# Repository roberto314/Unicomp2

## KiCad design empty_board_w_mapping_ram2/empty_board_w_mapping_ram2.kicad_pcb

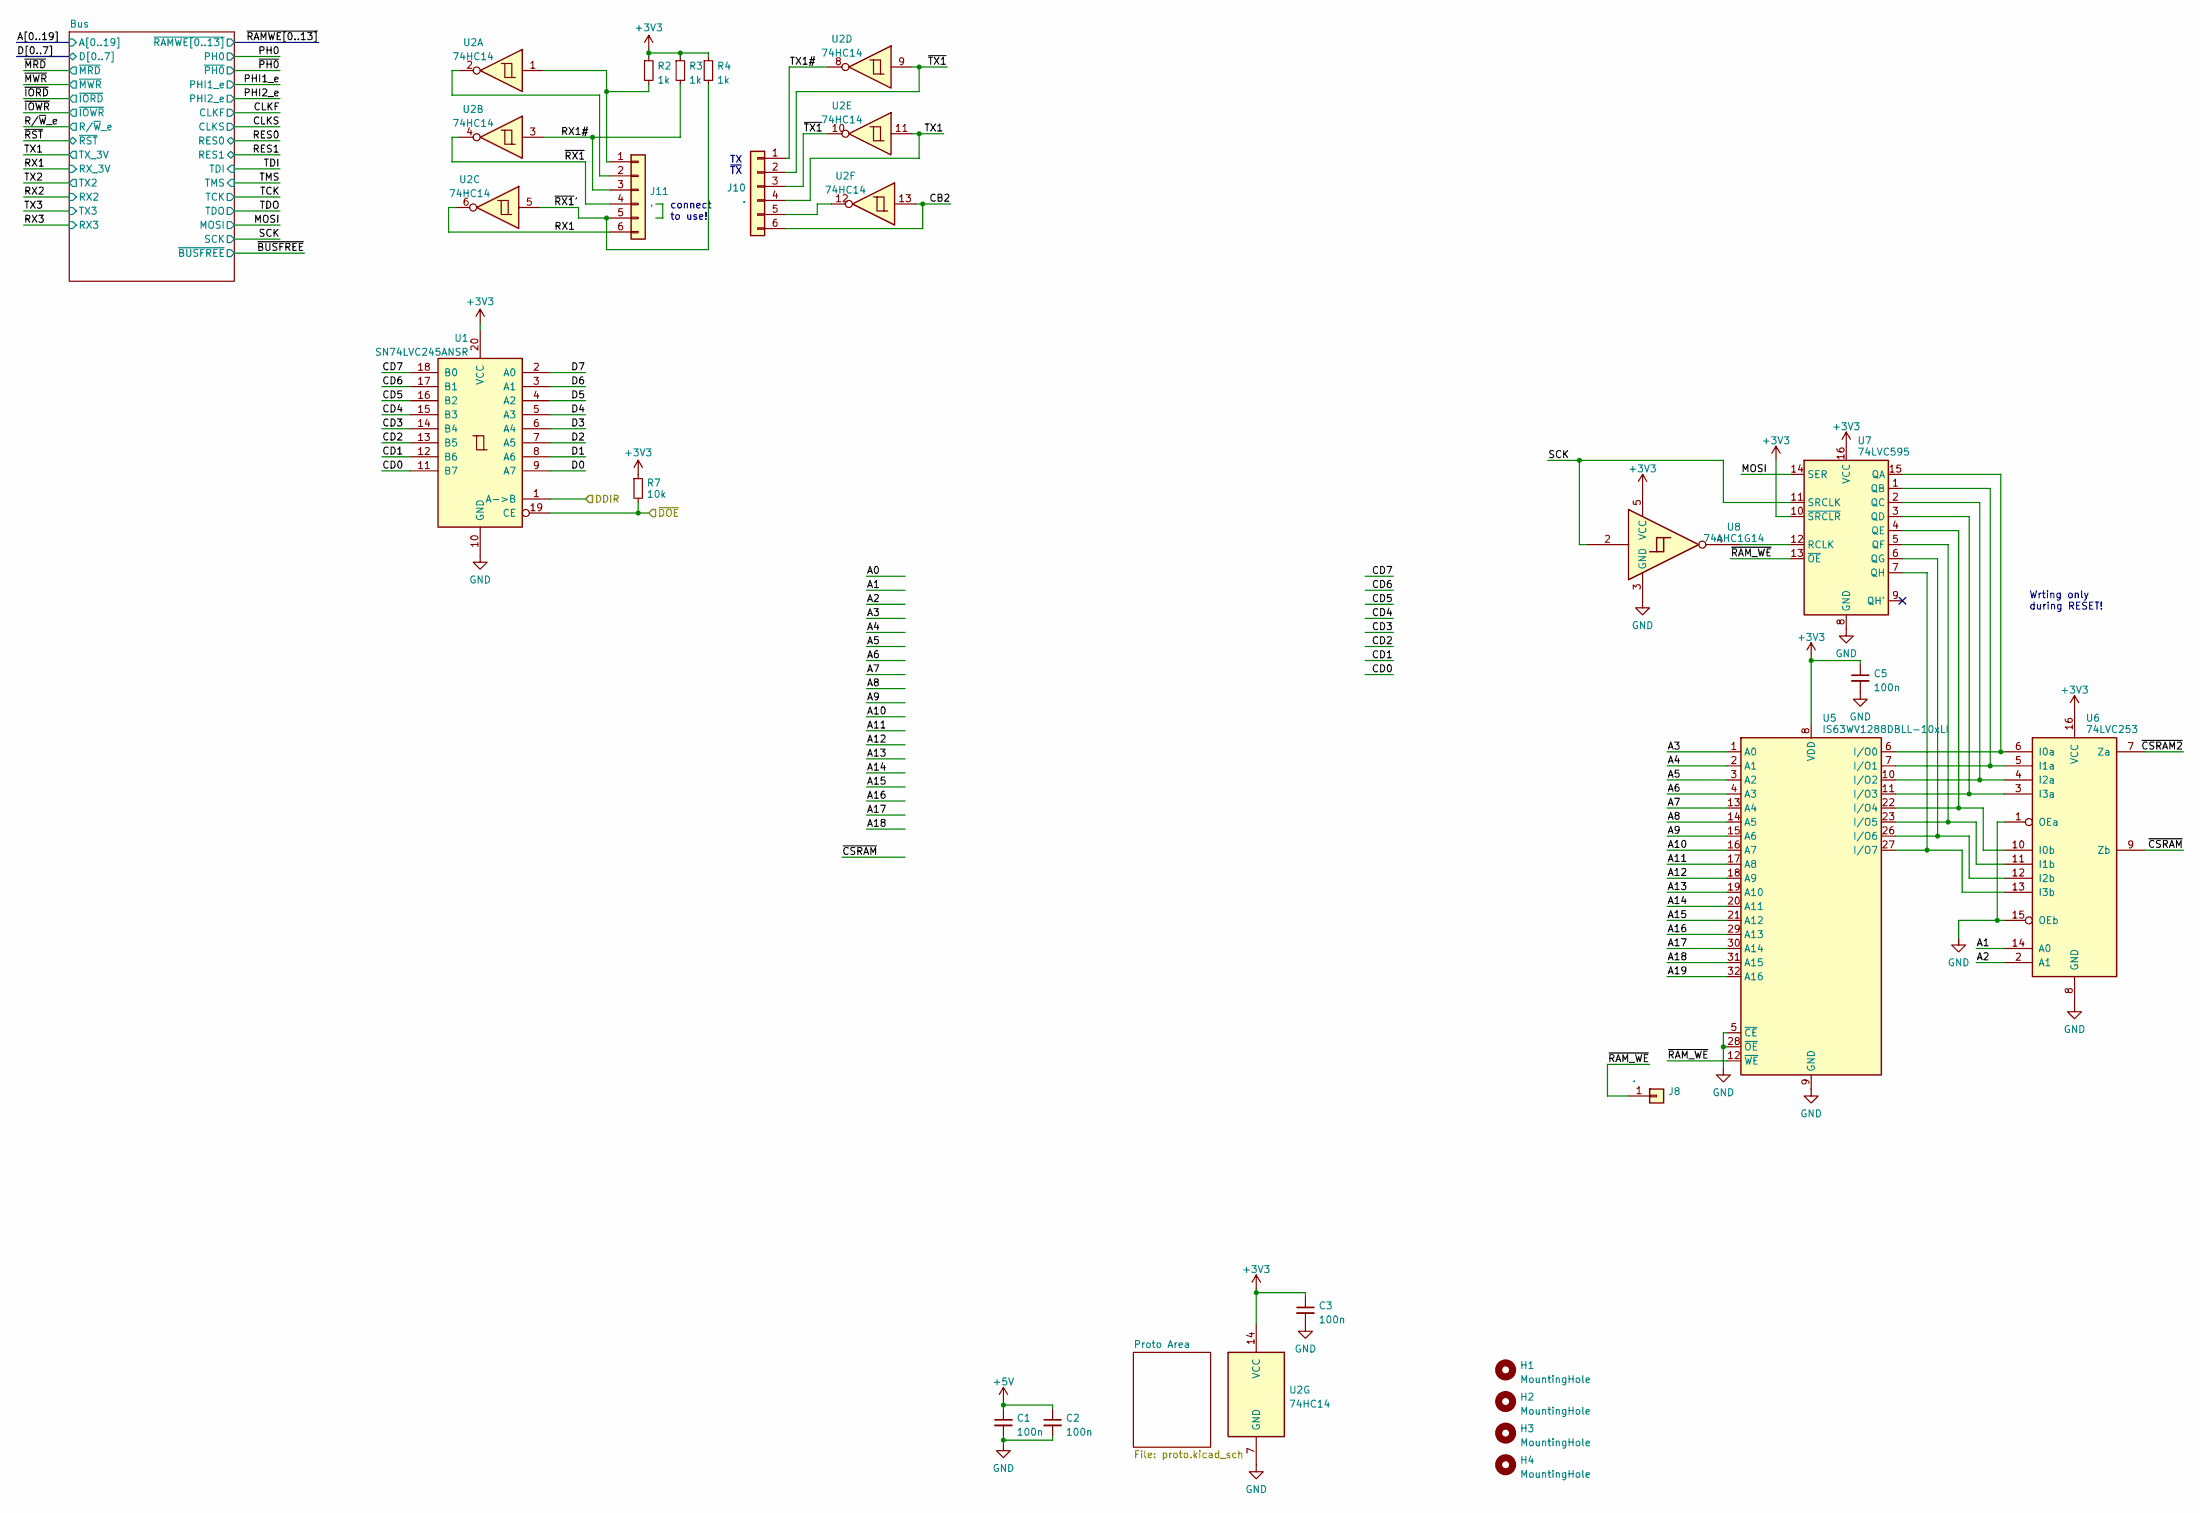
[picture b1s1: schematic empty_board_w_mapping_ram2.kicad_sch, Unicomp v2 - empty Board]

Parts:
C1, C2, C3, C5: 100n; C_1206_3216Metric
H1, H2, H3, H4: MountingHole; MountingHole_3.2mm_M3
J8: .; PinHeader_1x01_P2.00mm_Vertical
J10, J11: .; PinHeader_1x06_P2.54mm_Vertical
R2, R3, R4: 1k; R_1206_3216Metric_Pad1.30x1.75mm_HandSolder
R7: 10k; R_1206_3216Metric_Pad1.30x1.75mm_HandSolder
U1: SN74LVC245ANSR; SO-20_5.3x12.6mm_P1.27mm
U2: 74HC14; DIP-14_W7.62mm_Socket
U5: IS63WV1288DBLL-10xLI; TSOP-II-32_21.0x10.2mm_P1.27mm
U6: 74LVC253; SO-16_3.9x9.9mm_P1.27mm
U7: 74LVC595; SO-16_3.9x9.9mm_P1.27mm
U8: 74AHC1G14; SOT-23-5

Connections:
+3V3: C3.1, C5.1, R2.1, R3.1, R4.1, R7.1, U1.20 (VCC), U2.14 (VCC), U5.8 (VDD), U5.24 (VDD), U6.16 (VCC), U7.10 (~SRCLR), U7.16 (VCC), U8.5 (VCC); also elsewhere on the board
+5V: C1.1, C2.1; also elsewhere on the board
/A1: U6.14 (A0); also elsewhere on the board
/A2: U6.2 (A1); also elsewhere on the board
/A3: U5.1 (A0); also elsewhere on the board
/A4: U5.2 (A1); also elsewhere on the board
/A5: U5.3 (A2); also elsewhere on the board
/A6: U5.4 (A3); also elsewhere on the board
/A7: U5.13 (A4); also elsewhere on the board
/A8: U5.14 (A5); also elsewhere on the board
/A9: U5.15 (A6); also elsewhere on the board
/A10: U5.16 (A7); also elsewhere on the board
/A11: U5.17 (A8); also elsewhere on the board
/A12: U5.18 (A9); also elsewhere on the board
/A13: U5.19 (A10); also elsewhere on the board
/A14: U5.20 (A11); also elsewhere on the board
/A15: U5.21 (A12); also elsewhere on the board
/A16: U5.29 (A13); also elsewhere on the board
/A17: U5.30 (A14); also elsewhere on the board
/A18: U5.31 (A15); also elsewhere on the board
/A19: U5.32 (A16); also elsewhere on the board
/CB2: J10.6, U2.13
/CD0: U1.11 (B7)
/CD1: U1.12 (B6)
/CD2: U1.13 (B5)
/CD3: U1.14 (B4)
/CD4: U1.15 (B3)
/CD5: U1.16 (B2)
/CD6: U1.17 (B1)
/CD7: U1.18 (B0)
/D0: U1.9 (A7); also elsewhere on the board
/D1: U1.8 (A6); also elsewhere on the board
/D2: U1.7 (A5); also elsewhere on the board
/D3: U1.6 (A4); also elsewhere on the board
/D4: U1.5 (A3); also elsewhere on the board
/D5: U1.4 (A2); also elsewhere on the board
/D6: U1.3 (A1); also elsewhere on the board
/D7: U1.2 (A0); also elsewhere on the board
/DDIR: U1.1 (A->B)
/MOSI: U7.14 (SER); also elsewhere on the board
/RX1: J11.6, U2.6; also elsewhere on the board
/RX1#: J11.3, R3.2, U2.3
/SCK: U7.11 (SRCLK), U8.2; also elsewhere on the board
/TX1: J10.4, U2.11; also elsewhere on the board
/TX1#: J10.1, U2.8
/~CSRAM2: U6.7 (Za)
/~CSRAM: U6.9 (Zb)
/~DOE: R7.2, U1.19 (CE)
/~RAM_WE: J8.1, U5.12 (~WE), U7.13 (~OE)
/~RX1: J11.4, U2.4
/~RX1': J11.5, R4.2, U2.5
/~TX1: J10.2, J10.3, U2.9, U2.10
GND: C1.2, C2.2, C3.2, C5.2, U1.10 (GND), U2.7 (GND), U5.5 (~CE), U5.9 (GND), U5.25 (GND), U5.28 (~OE), U6.1 (OEa), U6.8 (GND), U6.15 (OEb), U7.8 (GND), U8.3 (GND); also elsewhere on the board
unnamed: J10.5, U2.12
unnamed: J11.1, R2.2, U2.1
unnamed: J11.2, U2.2
unnamed: U5.6 (I/O0), U6.6 (I0a), U7.15 (QA)
unnamed: U5.7 (I/O1), U6.5 (I1a), U7.1 (QB)
unnamed: U5.10 (I/O2), U6.4 (I2a), U7.2 (QC)
unnamed: U5.11 (I/O3), U6.3 (I3a), U7.3 (QD)
unnamed: U5.22 (I/O4), U6.10 (I0b), U7.4 (QE)
unnamed: U5.23 (I/O5), U6.11 (I1b), U7.5 (QF)
unnamed: U5.26 (I/O6), U6.12 (I2b), U7.6 (QG)
unnamed: U5.27 (I/O7), U6.13 (I3b), U7.7 (QH)
unnamed: U7.12 (RCLK), U8.4

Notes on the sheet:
Wrting only during RESET!
connect to use!
TX ~{TX}

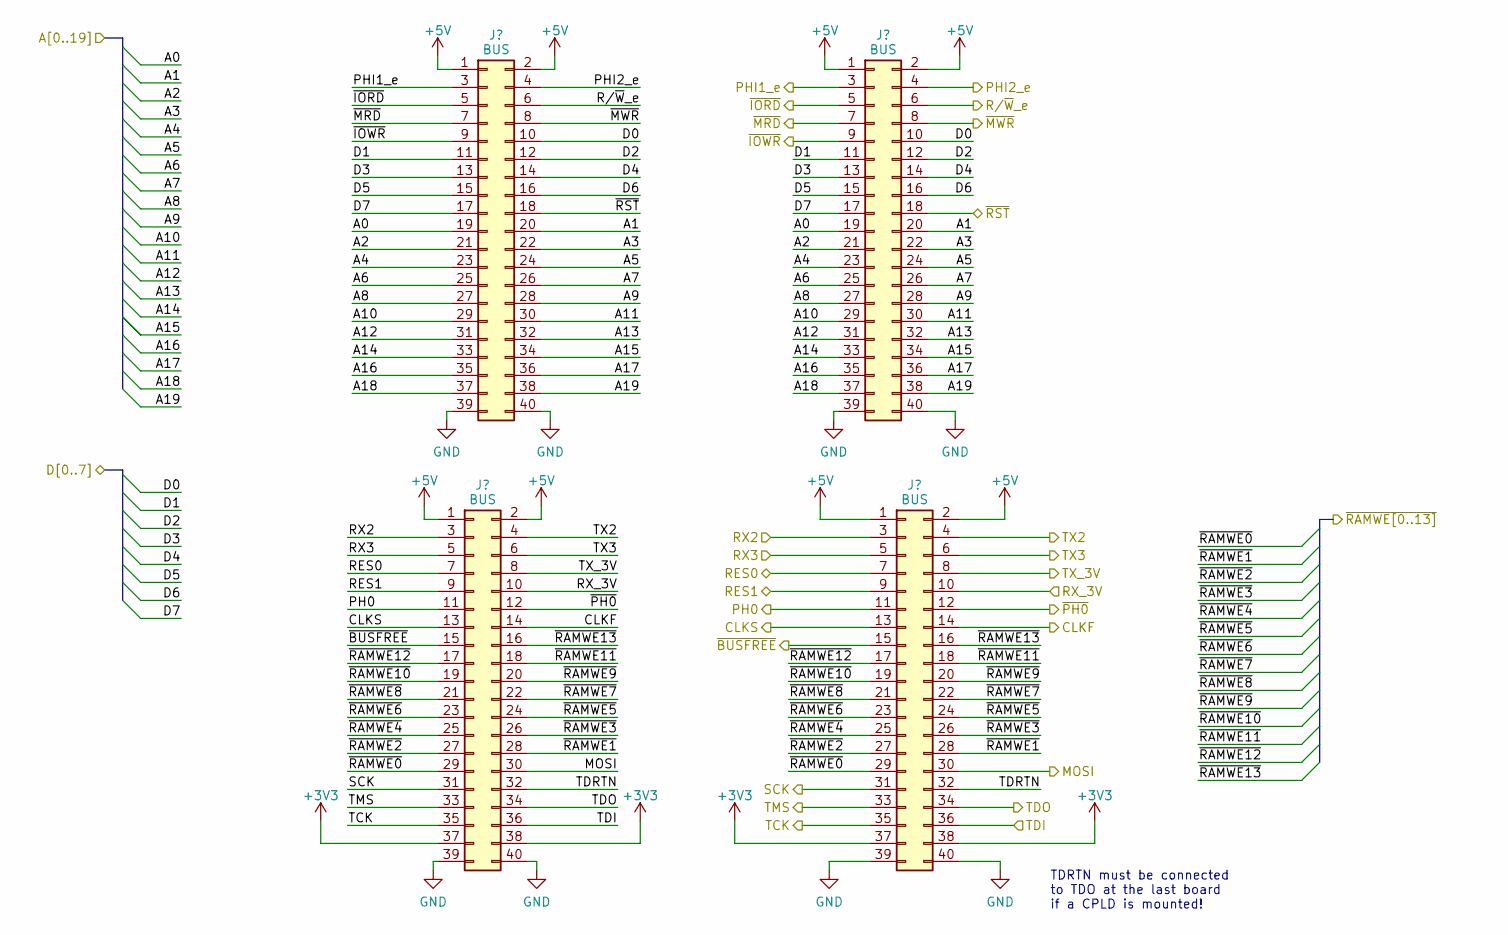
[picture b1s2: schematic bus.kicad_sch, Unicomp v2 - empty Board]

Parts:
J1, J2, J3, J4: BUS; PinSocket_2x20_P2.54mm_Vertical

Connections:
+3V3: J2.37, J2.38, J4.37, J4.38; also elsewhere on the board
+5V: J1.1, J1.2, J2.1, J2.2, J3.1, J3.2, J4.1, J4.2; also elsewhere on the board
/A0: J1.19, J3.19
/A1: J1.20, J3.20; also elsewhere on the board
/A2: J1.21, J3.21; also elsewhere on the board
/A3: J1.22, J3.22; also elsewhere on the board
/A4: J1.23, J3.23; also elsewhere on the board
/A5: J1.24, J3.24; also elsewhere on the board
/A6: J1.25, J3.25; also elsewhere on the board
/A7: J1.26, J3.26; also elsewhere on the board
/A8: J1.27, J3.27; also elsewhere on the board
/A9: J1.28, J3.28; also elsewhere on the board
/A10: J1.29, J3.29; also elsewhere on the board
/A11: J1.30, J3.30; also elsewhere on the board
/A12: J1.31, J3.31; also elsewhere on the board
/A13: J1.32, J3.32; also elsewhere on the board
/A14: J1.33, J3.33; also elsewhere on the board
/A15: J1.34, J3.34; also elsewhere on the board
/A16: J1.35, J3.35; also elsewhere on the board
/A17: J1.36, J3.36; also elsewhere on the board
/A18: J1.37, J3.37; also elsewhere on the board
/A19: J1.38, J3.38; also elsewhere on the board
/Bus/TDRTN: J2.32, J4.32
/CLKF: J2.14, J4.14
/CLKS: J2.13, J4.13
/D0: J1.10, J3.10; also elsewhere on the board
/D1: J1.11, J3.11; also elsewhere on the board
/D2: J1.12, J3.12; also elsewhere on the board
/D3: J1.13, J3.13; also elsewhere on the board
/D4: J1.14, J3.14; also elsewhere on the board
/D5: J1.15, J3.15; also elsewhere on the board
/D6: J1.16, J3.16; also elsewhere on the board
/D7: J1.17, J3.17; also elsewhere on the board
/MOSI: J2.30, J4.30; also elsewhere on the board
/PH0: J2.11, J4.11
/PHI1_e: J1.3, J3.3
/PHI2_e: J1.4, J3.4
/RES0: J2.7, J4.7
/RES1: J2.9, J4.9
/RX1: J2.10, J4.10; also elsewhere on the board
/RX2: J2.3, J4.3
/RX3: J2.5, J4.5
/R/~W_e: J1.6, J3.6
/SCK: J2.31, J4.31; also elsewhere on the board
/TCK: J2.35, J4.35
/TDI: J2.36, J4.36
/TDO: J2.34, J4.34
/TMS: J2.33, J4.33
/TX1: J2.8, J4.8; also elsewhere on the board
/TX2: J2.4, J4.4
/TX3: J2.6, J4.6
/~BUSFREE: J2.15, J4.15
/~IORD: J1.5, J3.5
/~IOWR: J1.9, J3.9
/~MRD: J1.7, J3.7
/~MWR: J1.8, J3.8
/~PH0: J2.12, J4.12
/~RAMWE0: J2.29, J4.29
/~RAMWE1: J2.28, J4.28
/~RAMWE2: J2.27, J4.27
/~RAMWE3: J2.26, J4.26
/~RAMWE4: J2.25, J4.25
/~RAMWE5: J2.24, J4.24
/~RAMWE6: J2.23, J4.23
/~RAMWE7: J2.22, J4.22
/~RAMWE8: J2.21, J4.21
/~RAMWE9: J2.20, J4.20
/~RAMWE10: J2.19, J4.19
/~RAMWE11: J2.18, J4.18
/~RAMWE12: J2.17, J4.17
/~RAMWE13: J2.16, J4.16
/~RST: J1.18, J3.18
GND: J1.39, J1.40, J2.39, J2.40, J3.39, J3.40, J4.39, J4.40; also elsewhere on the board

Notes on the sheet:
TDRTN must be connected to TDO at the last board if a CPLD is mounted!

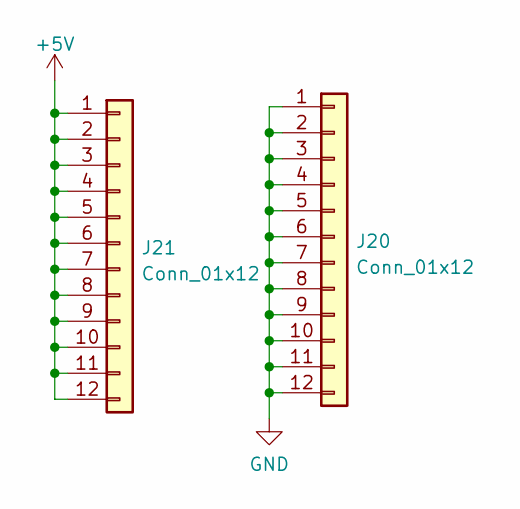
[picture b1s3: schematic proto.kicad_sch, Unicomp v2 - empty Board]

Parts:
J20, J21: Conn_01x12; PinHeader_1x12_P2.54mm_Vertical

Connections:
+5V: J21.1, J21.2, J21.3, J21.4, J21.5, J21.6, J21.7, J21.8, J21.9, J21.10, J21.11, J21.12; also elsewhere on the board
GND: J20.1, J20.2, J20.3, J20.4, J20.5, J20.6, J20.7, J20.8, J20.9, J20.10, J20.11, J20.12; also elsewhere on the board

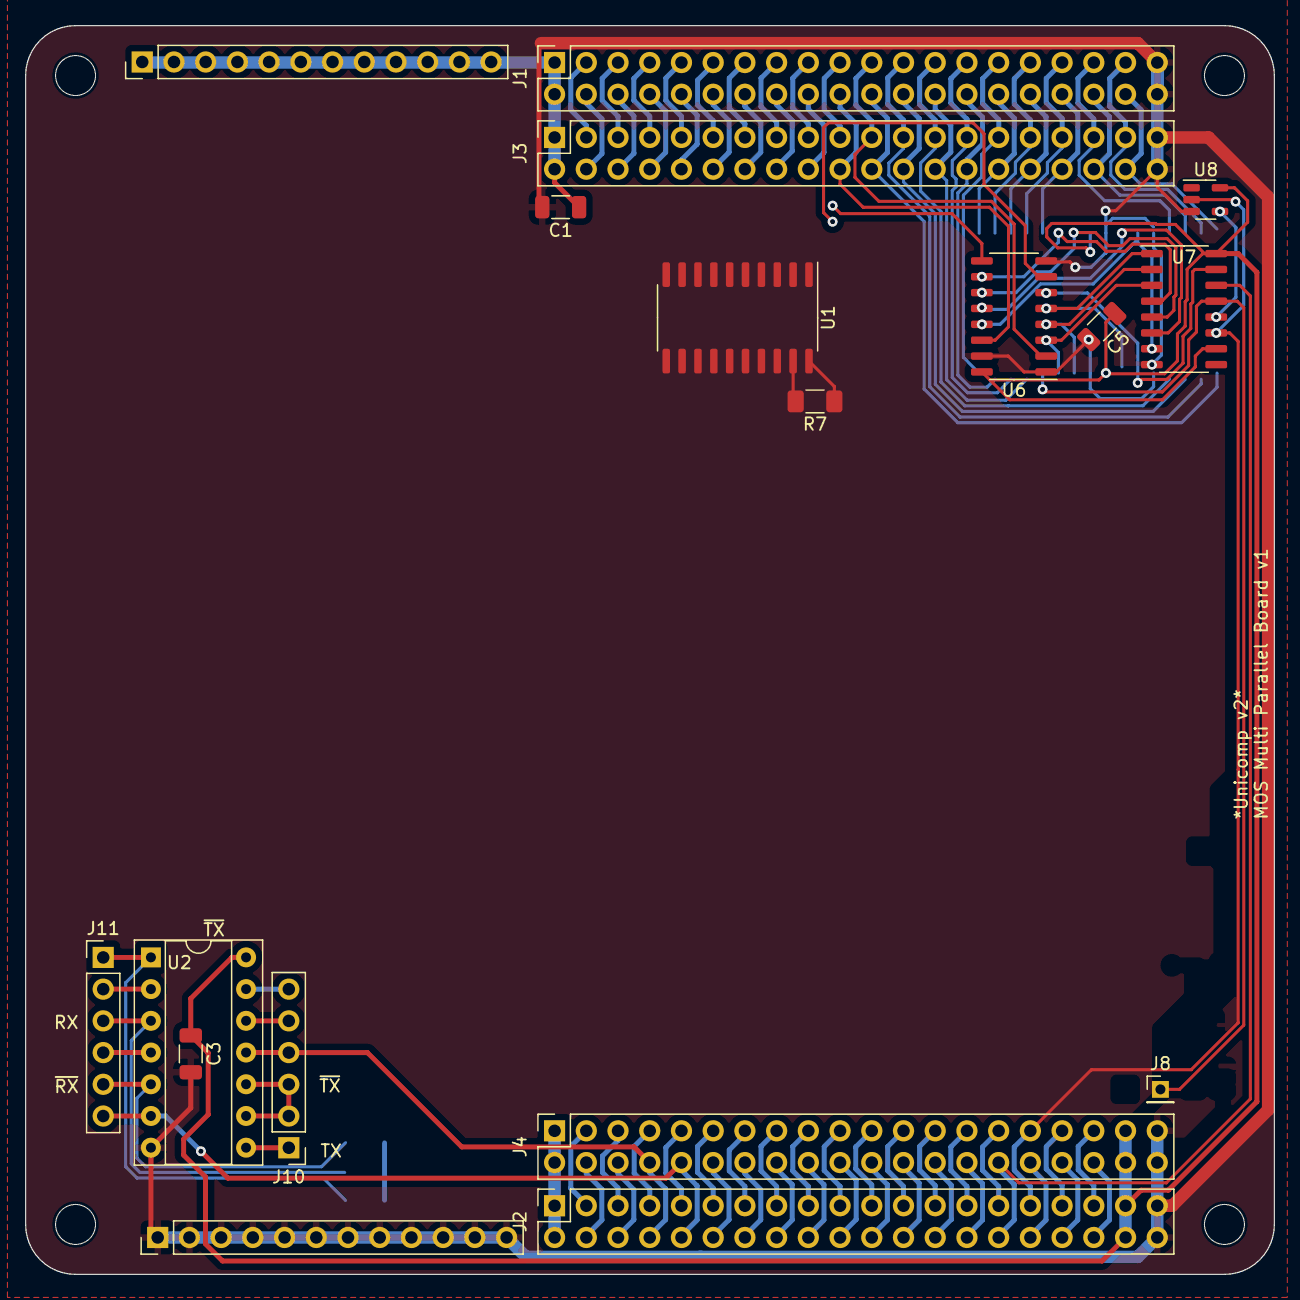
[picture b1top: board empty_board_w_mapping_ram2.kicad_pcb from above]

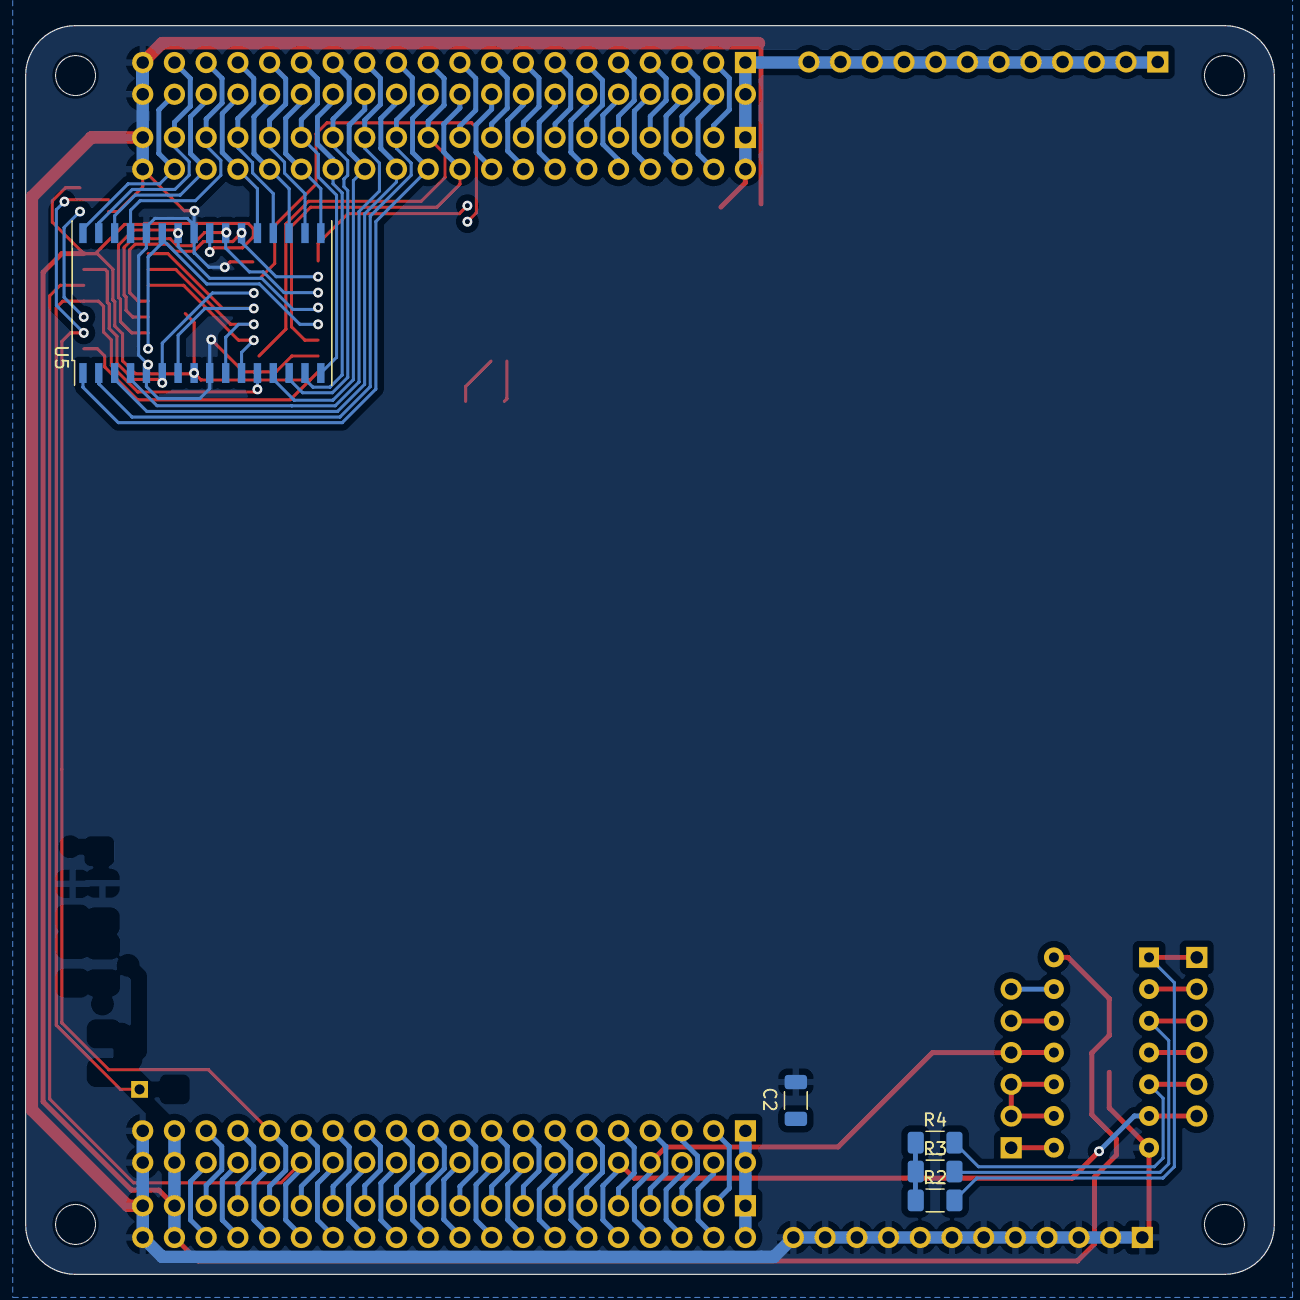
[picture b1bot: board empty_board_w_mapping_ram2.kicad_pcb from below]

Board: 2 copper layers, 100.0 x 100.0 mm, 27 parts (5 on the bottom side), 93 nets.

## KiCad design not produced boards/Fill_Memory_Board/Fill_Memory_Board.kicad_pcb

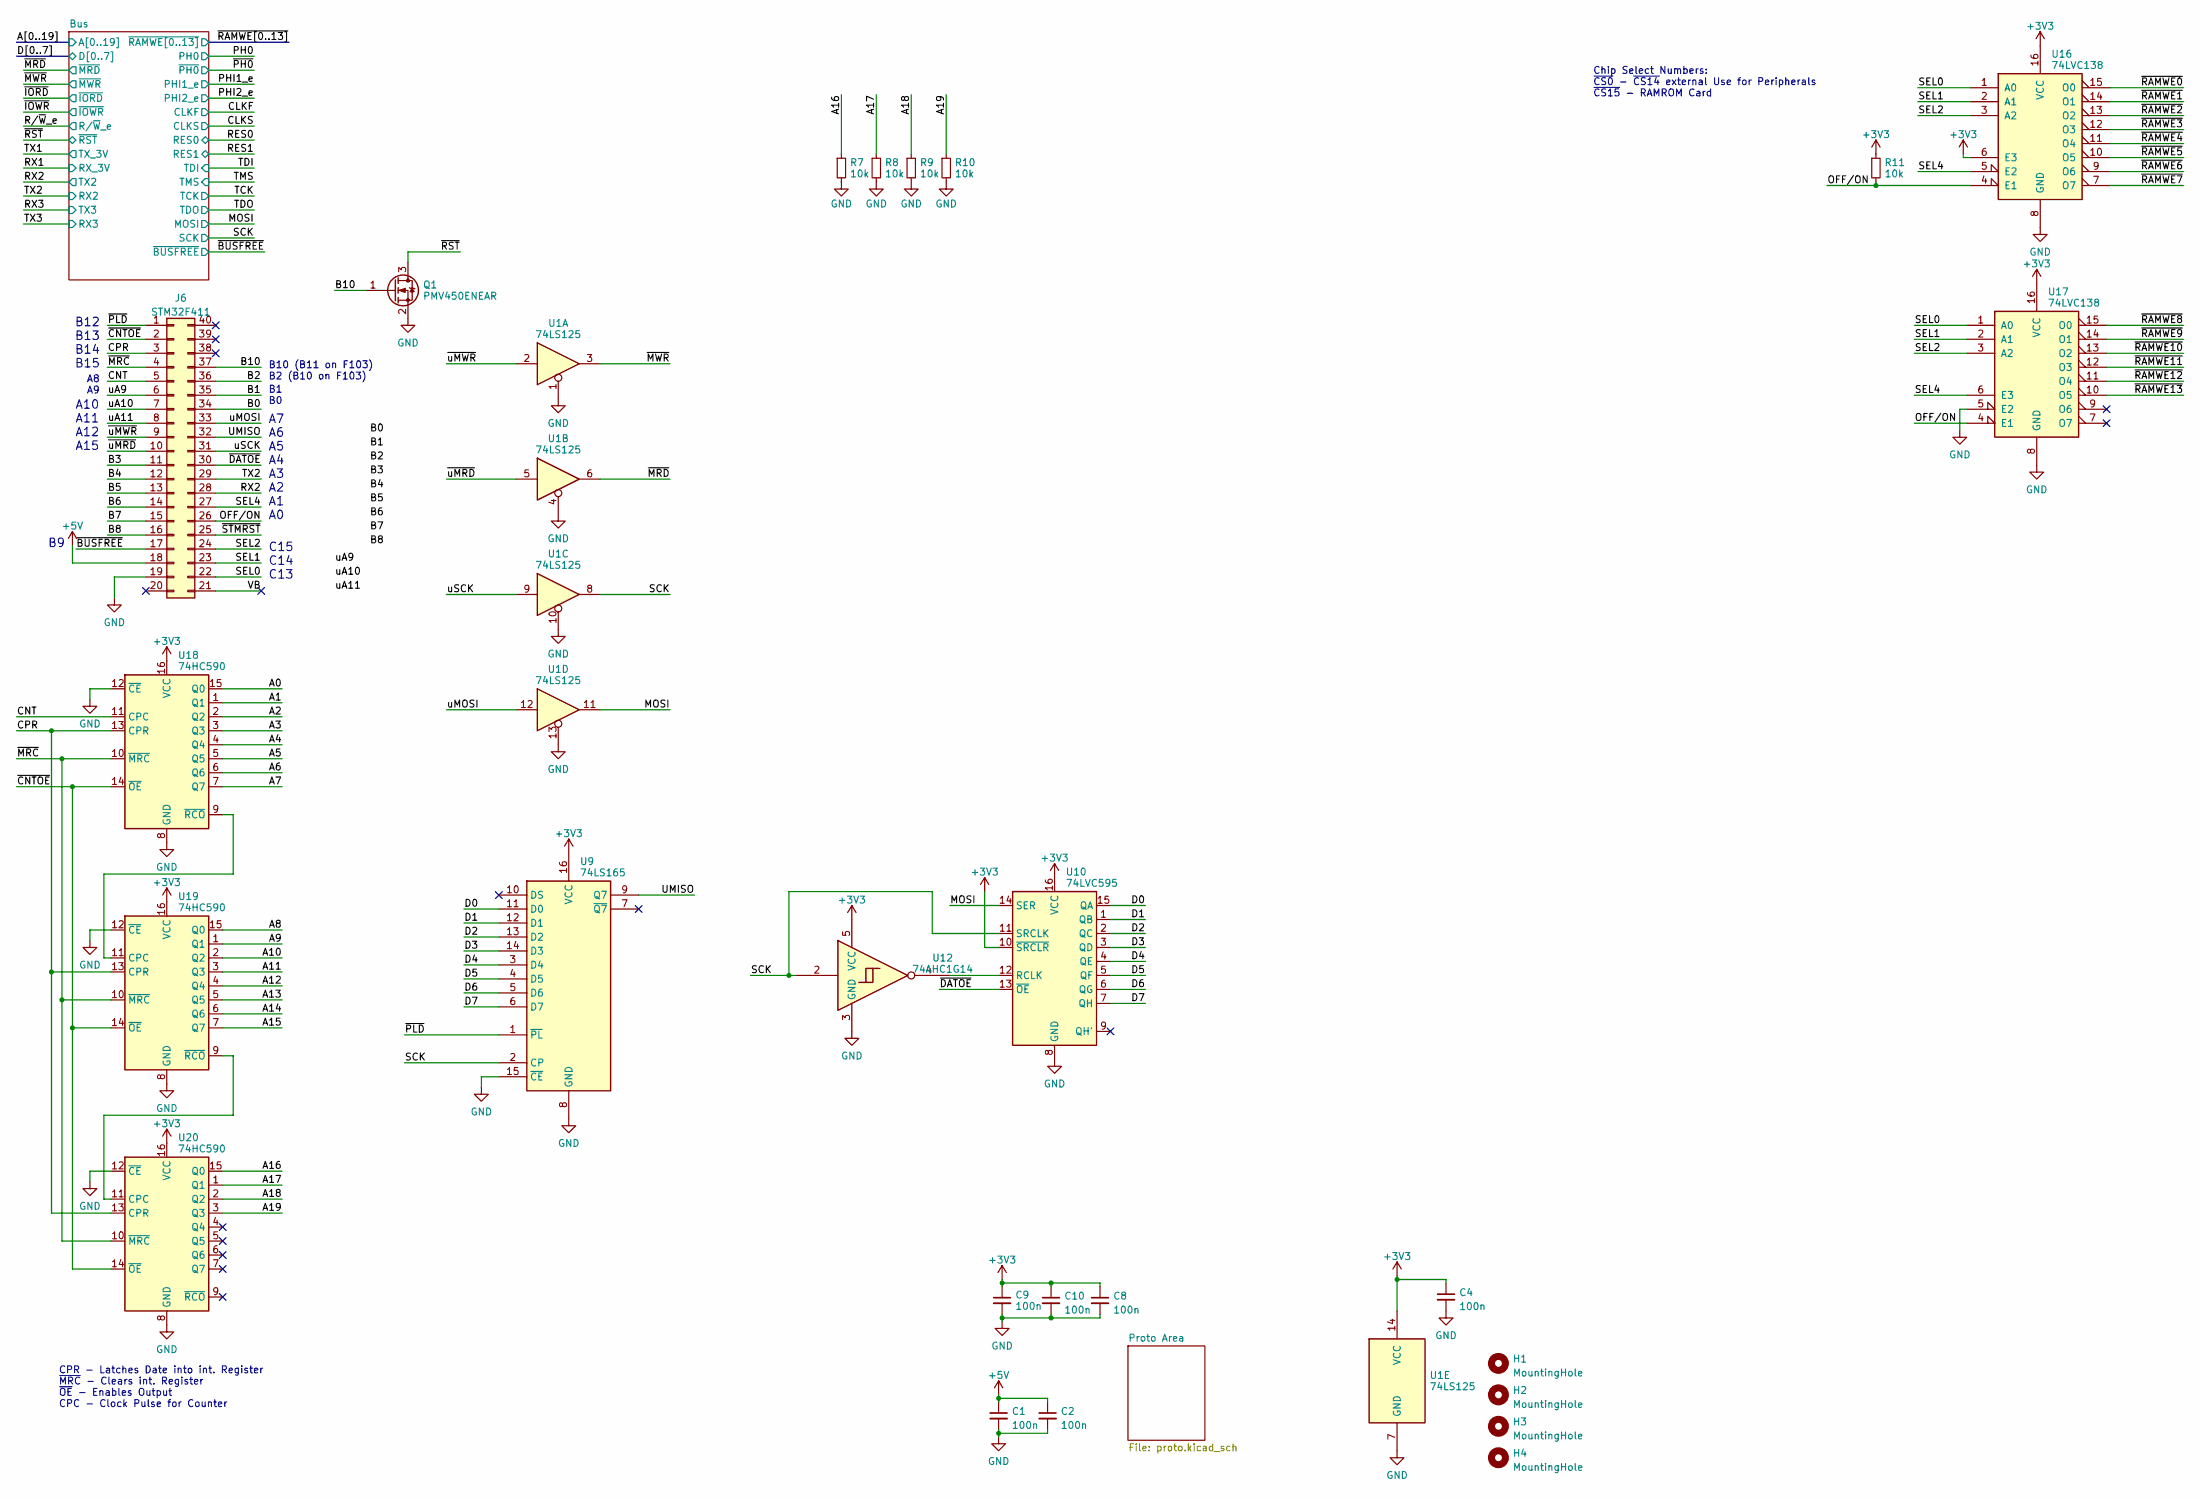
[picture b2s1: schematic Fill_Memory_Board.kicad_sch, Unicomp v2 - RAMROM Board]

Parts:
C1, C2, C4, C8, C9, C10: 100n; C_1206_3216Metric
H1, H2, H3, H4: MountingHole; MountingHole_3.2mm_M3
J6: STM32F411; DIP-40_W15.24mm_Socket_LongPads
Q1: PMV450ENEAR; SOT-23
R7, R8, R9, R10, R11: 10k; R_1206_3216Metric_Pad1.30x1.75mm_HandSolder
U1: 74LS125; SOIC-14_3.9x8.7mm_P1.27mm
U9: 74LS165; SOIC-16_3.9x9.9mm_P1.27mm
U10: 74LVC595; SO-16_3.9x9.9mm_P1.27mm
U12: 74AHC1G14; SOT-23-5
U16, U17: 74LVC138; SOIC-16_3.9x9.9mm_P1.27mm
U18, U19, U20: 74HC590; SOIC-16_3.9x9.9mm_P1.27mm

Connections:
+3V3: C4.1, C8.1, C9.1, C10.1, R11.1, U1.14 (VCC), U9.16 (VCC), U10.10 (~SRCLR), U10.16 (VCC), U12.5 (VCC), U16.6 (E3), U16.16 (VCC), U17.16 (VCC), U18.16 (VCC), U19.16 (VCC), U20.16 (VCC); also elsewhere on the board
+5V: C1.1, C2.1, J6.18; also elsewhere on the board
/A0: U18.15 (Q0); also elsewhere on the board
/A1: U18.1 (Q1); also elsewhere on the board
/A2: U18.2 (Q2); also elsewhere on the board
/A3: U18.3 (Q3); also elsewhere on the board
/A4: U18.4 (Q4); also elsewhere on the board
/A5: U18.5 (Q5); also elsewhere on the board
/A6: U18.6 (Q6); also elsewhere on the board
/A7: U18.7 (Q7); also elsewhere on the board
/A8: U19.15 (Q0); also elsewhere on the board
/A9: U19.1 (Q1); also elsewhere on the board
/A10: U19.2 (Q2); also elsewhere on the board
/A11: U19.3 (Q3); also elsewhere on the board
/A12: U19.4 (Q4); also elsewhere on the board
/A13: U19.5 (Q5); also elsewhere on the board
/A14: U19.6 (Q6); also elsewhere on the board
/A15: U19.7 (Q7); also elsewhere on the board
/A16: R7.1, U20.15 (Q0); also elsewhere on the board
/A17: R8.1, U20.1 (Q1); also elsewhere on the board
/A18: R9.1, U20.2 (Q2); also elsewhere on the board
/A19: R10.1, U20.3 (Q3); also elsewhere on the board
/B0: J6.34
/B1: J6.35
/B2: J6.36
/B3: J6.11
/B4: J6.12
/B5: J6.13
/B6: J6.14
/B7: J6.15
/B8: J6.16
/B10: J6.37, Q1.1 (G)
/CNT: J6.5, U18.11 (CPC)
/CPR: J6.3, U18.13 (CPR), U19.13 (CPR), U20.13 (CPR)
/D0: U9.11 (D0), U10.15 (QA); also elsewhere on the board
/D1: U9.12 (D1), U10.1 (QB); also elsewhere on the board
/D2: U9.13 (D2), U10.2 (QC); also elsewhere on the board
/D3: U9.14 (D3), U10.3 (QD); also elsewhere on the board
/D4: U9.3 (D4), U10.4 (QE); also elsewhere on the board
/D5: U9.4 (D5), U10.5 (QF); also elsewhere on the board
/D6: U9.5 (D6), U10.6 (QG); also elsewhere on the board
/D7: U9.6 (D7), U10.7 (QH); also elsewhere on the board
/MOSI: U1.11, U10.14 (SER); also elsewhere on the board
/OFF/ON: J6.26, R11.2, U16.4 (E1), U17.4 (E1)
/RX2: J6.28; also elsewhere on the board
/SCK: U1.8, U9.2 (CP), U10.11 (SRCLK), U12.2; also elsewhere on the board
/SEL0: J6.22, U16.1 (A0), U17.1 (A0)
/SEL1: J6.23, U16.2 (A1), U17.2 (A1)
/SEL2: J6.24, U16.3 (A2), U17.3 (A2)
/SEL4: J6.27, U16.5 (E2), U17.6 (E3)
/TX2: J6.29; also elsewhere on the board
/UMISO: J6.32, U9.9 (Q7)
/VB: J6.21
/uA9: J6.6
/uA10: J6.7
/uA11: J6.8
/uMOSI: J6.33, U1.12
/uSCK: J6.31, U1.9
/~BUSFREE: J6.17; also elsewhere on the board
/~CNTOE: J6.2, U18.14 (~OE), U19.14 (~OE), U20.14 (~OE)
/~DATOE: J6.30, U10.13 (~OE)
/~MRC: J6.4, U18.10 (~MRC), U19.10 (~MRC), U20.10 (~MRC)
/~MRD: U1.6; also elsewhere on the board
/~MWR: U1.3; also elsewhere on the board
/~PLD: J6.1, U9.1 (~PL)
/~RAMWE0: U16.15 (O0); also elsewhere on the board
/~RAMWE1: U16.14 (O1); also elsewhere on the board
/~RAMWE2: U16.13 (O2); also elsewhere on the board
/~RAMWE3: U16.12 (O3); also elsewhere on the board
/~RAMWE4: U16.11 (O4); also elsewhere on the board
/~RAMWE5: U16.10 (O5); also elsewhere on the board
/~RAMWE6: U16.9 (O6); also elsewhere on the board
/~RAMWE7: U16.7 (O7); also elsewhere on the board
/~RAMWE8: U17.15 (O0); also elsewhere on the board
/~RAMWE9: U17.14 (O1); also elsewhere on the board
/~RAMWE10: U17.13 (O2); also elsewhere on the board
/~RAMWE11: U17.12 (O3); also elsewhere on the board
/~RAMWE12: U17.11 (O4); also elsewhere on the board
/~RAMWE13: U17.10 (O5); also elsewhere on the board
/~RST: Q1.3 (D); also elsewhere on the board
/~STMRST: J6.25
/~uMRD: J6.10, U1.5
/~uMWR: J6.9, U1.2
GND: C1.2, C2.2, C4.2, C8.2, C9.2, C10.2, J6.19, Q1.2 (S), R7.2, R8.2, R9.2, R10.2, U1.1, U1.4, U1.7 (GND), U1.10, U1.13, U9.8 (GND), U9.15 (~CE), U10.8 (GND), U12.3 (GND), U16.8 (GND), U17.5 (E2), U17.8 (GND), U18.8 (GND), U18.12 (~CE), U19.8 (GND), U19.12 (~CE), U20.8 (GND), U20.12 (~CE); also elsewhere on the board
unnamed: U10.12 (RCLK), U12.4
unnamed: U18.9 (~RCO), U19.11 (CPC)
unnamed: U19.9 (~RCO), U20.11 (CPC)

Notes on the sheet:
B10 (B11 on F103) B2 (B10 on F103)
B12 B13 B14 B15
A10 A11 A12 A15
B1 B0
C15 C14 C13
A8 A9
CPR - Latches Date into int. Register ~{MRC} - Clears int. Register ~{OE} - Enables Output CPC - Clock Pulse for Counter
A7 A6 A5 A4 A3 A2 A1 A0
Chip Select Numbers: ~{CS0} - ~{CS14} external Use for Peripherals ~{CS15} - RAMROM Card

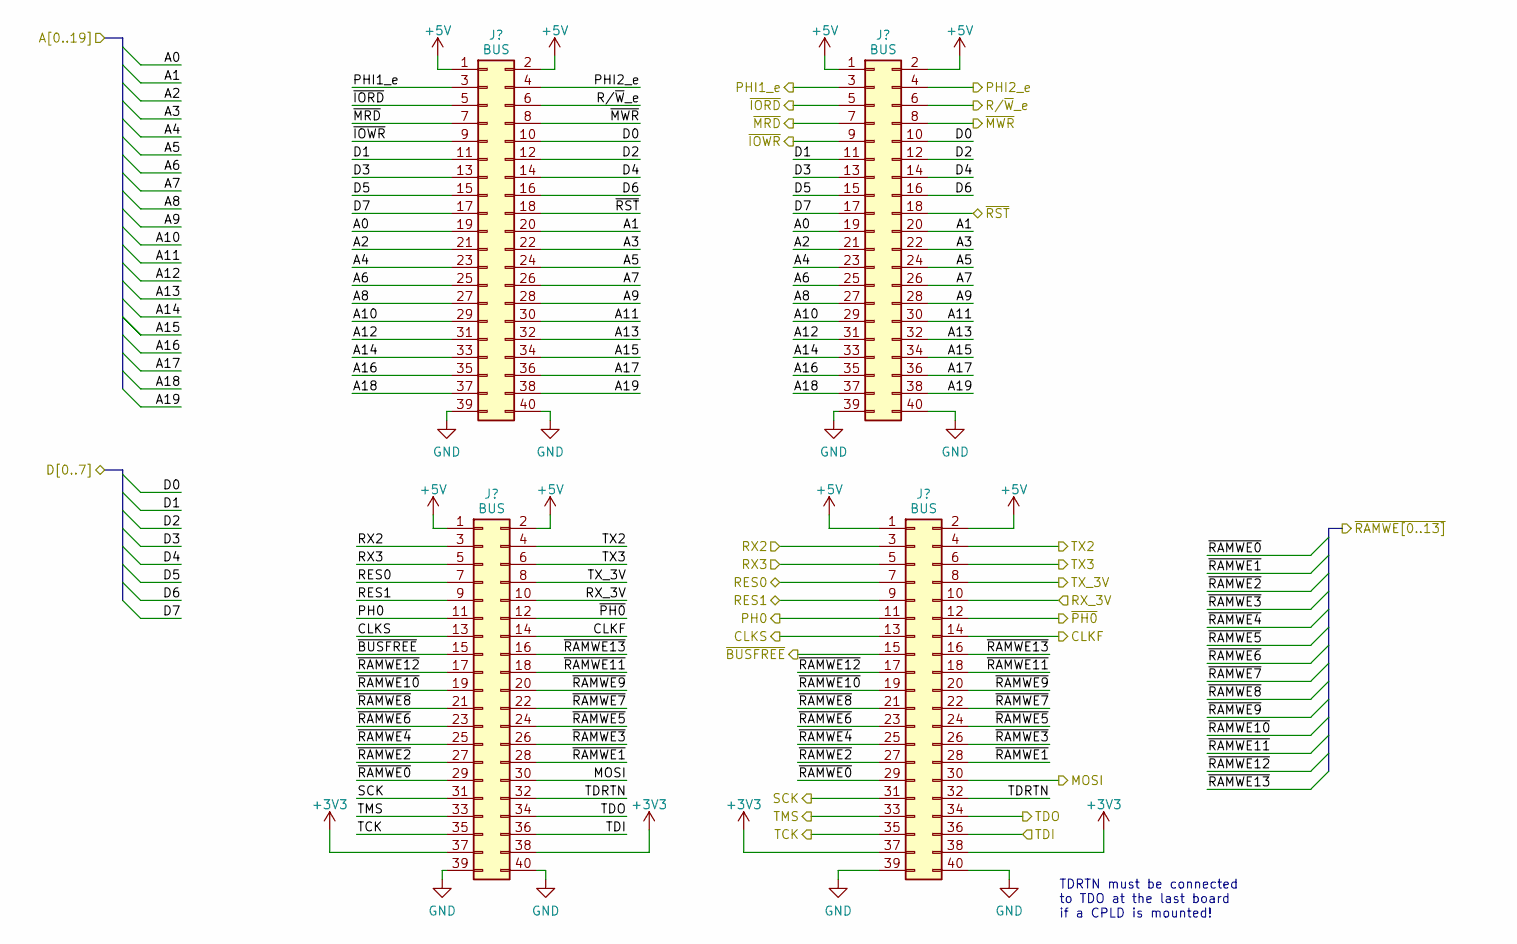
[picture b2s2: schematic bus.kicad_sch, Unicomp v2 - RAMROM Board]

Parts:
J1, J2, J3, J4: BUS; PinSocket_2x20_P2.54mm_Vertical

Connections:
+3V3: J2.37, J2.38, J4.37, J4.38; also elsewhere on the board
+5V: J1.1, J1.2, J2.1, J2.2, J3.1, J3.2, J4.1, J4.2; also elsewhere on the board
/A0: J1.19, J3.19; also elsewhere on the board
/A1: J1.20, J3.20; also elsewhere on the board
/A2: J1.21, J3.21; also elsewhere on the board
/A3: J1.22, J3.22; also elsewhere on the board
/A4: J1.23, J3.23; also elsewhere on the board
/A5: J1.24, J3.24; also elsewhere on the board
/A6: J1.25, J3.25; also elsewhere on the board
/A7: J1.26, J3.26; also elsewhere on the board
/A8: J1.27, J3.27; also elsewhere on the board
/A9: J1.28, J3.28; also elsewhere on the board
/A10: J1.29, J3.29; also elsewhere on the board
/A11: J1.30, J3.30; also elsewhere on the board
/A12: J1.31, J3.31; also elsewhere on the board
/A13: J1.32, J3.32; also elsewhere on the board
/A14: J1.33, J3.33; also elsewhere on the board
/A15: J1.34, J3.34; also elsewhere on the board
/A16: J1.35, J3.35; also elsewhere on the board
/A17: J1.36, J3.36; also elsewhere on the board
/A18: J1.37, J3.37; also elsewhere on the board
/A19: J1.38, J3.38; also elsewhere on the board
/Bus/TDRTN: J2.32, J4.32
/CLKF: J2.14, J4.14
/CLKS: J2.13, J4.13
/D0: J1.10, J3.10; also elsewhere on the board
/D1: J1.11, J3.11; also elsewhere on the board
/D2: J1.12, J3.12; also elsewhere on the board
/D3: J1.13, J3.13; also elsewhere on the board
/D4: J1.14, J3.14; also elsewhere on the board
/D5: J1.15, J3.15; also elsewhere on the board
/D6: J1.16, J3.16; also elsewhere on the board
/D7: J1.17, J3.17; also elsewhere on the board
/MOSI: J2.30, J4.30; also elsewhere on the board
/PH0: J2.11, J4.11
/PHI1_e: J1.3, J3.3
/PHI2_e: J1.4, J3.4
/RES0: J2.7, J4.7
/RES1: J2.9, J4.9
/RX1: J2.10, J4.10
/RX2: J2.3, J4.3; also elsewhere on the board
/RX3: J2.5, J4.5
/R/~W_e: J1.6, J3.6
/SCK: J2.31, J4.31; also elsewhere on the board
/TCK: J2.35, J4.35
/TDI: J2.36, J4.36
/TDO: J2.34, J4.34
/TMS: J2.33, J4.33
/TX1: J2.8, J4.8
/TX2: J2.4, J4.4; also elsewhere on the board
/TX3: J2.6, J4.6
/~BUSFREE: J2.15, J4.15; also elsewhere on the board
/~IORD: J1.5, J3.5
/~IOWR: J1.9, J3.9
/~MRD: J1.7, J3.7; also elsewhere on the board
/~MWR: J1.8, J3.8; also elsewhere on the board
/~PH0: J2.12, J4.12
/~RAMWE0: J2.29, J4.29; also elsewhere on the board
/~RAMWE1: J2.28, J4.28; also elsewhere on the board
/~RAMWE2: J2.27, J4.27; also elsewhere on the board
/~RAMWE3: J2.26, J4.26; also elsewhere on the board
/~RAMWE4: J2.25, J4.25; also elsewhere on the board
/~RAMWE5: J2.24, J4.24; also elsewhere on the board
/~RAMWE6: J2.23, J4.23; also elsewhere on the board
/~RAMWE7: J2.22, J4.22; also elsewhere on the board
/~RAMWE8: J2.21, J4.21; also elsewhere on the board
/~RAMWE9: J2.20, J4.20; also elsewhere on the board
/~RAMWE10: J2.19, J4.19; also elsewhere on the board
/~RAMWE11: J2.18, J4.18; also elsewhere on the board
/~RAMWE12: J2.17, J4.17; also elsewhere on the board
/~RAMWE13: J2.16, J4.16; also elsewhere on the board
/~RST: J1.18, J3.18; also elsewhere on the board
GND: J1.39, J1.40, J2.39, J2.40, J3.39, J3.40, J4.39, J4.40; also elsewhere on the board

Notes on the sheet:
TDRTN must be connected to TDO at the last board if a CPLD is mounted!
